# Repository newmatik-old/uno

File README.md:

# Uno

This is a complete package of files required to produce your own Arduino Uno. This serves as a demo repository for newmatik.com online PCBA customers to demo-price a project.

This package includes:

- CAD (Eagle board and schematic)
- Gerber Files
- PCB Specification
- Product Images
- Pick and Place File
- 3D Models

## Attributions

- Eagle board file and schematic, product image as well as dxf outlines from Arduino website (https://www.arduino.cc/en/Main/ArduinoBoardUno#documentation)

- Bill of Materials originally from Kitespace (https://github.com/kitspace-forks/arduino-uno)

- Collada and Sketchup 3D models from Trimble 3D Store, created by Engineer-Zero
  (https://3dwarehouse.sketchup.com/model/ee34d0b202060daa949ba13b9dbf2be2/Arduino-Uno?hl=de)

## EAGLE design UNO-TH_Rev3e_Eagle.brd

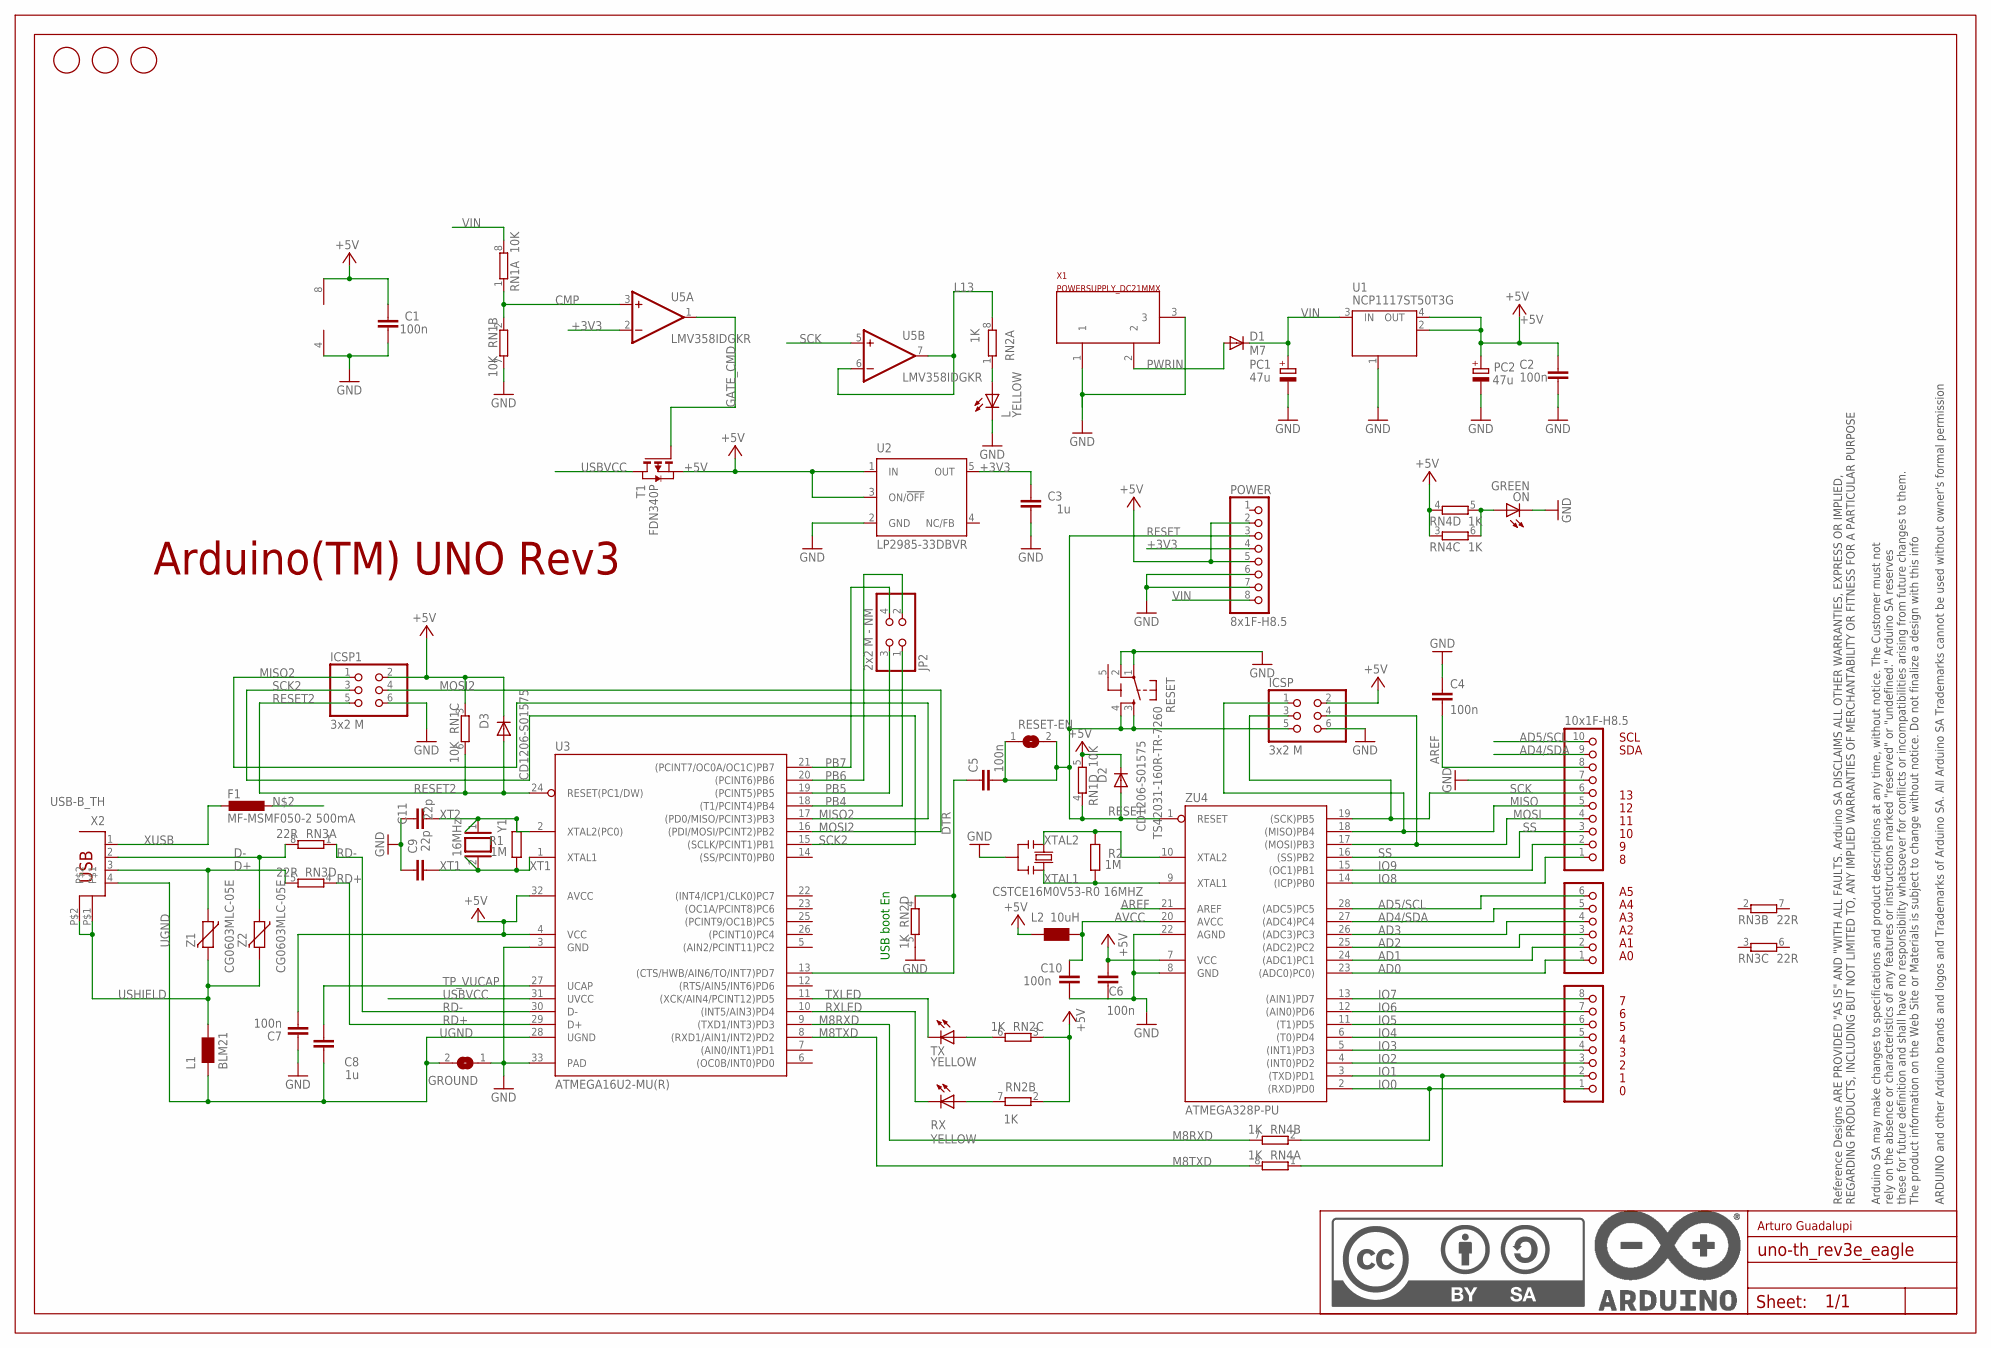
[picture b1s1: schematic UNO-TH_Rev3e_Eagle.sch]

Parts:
AD: 6x1F-H8.5; 1X06
C1, C2, C4, C5, C6, C7, C10: 100n; C0603-ROUND
C3, C8: 1u; C0603-ROUND
C9, C11: 22p; C0603-ROUND
D1: M7; SMB
D2, D3: CD1206-S01575; MINIMELF
F1: MF-MSMF050-2 500mA; L1812
FD1, FD2, FD3: FIDUCIALMOUNT; FIDUCIA-MOUNT
FRAME1: DNP; FRAME
GROUND: SJ
ICSP, ICSP1: 3x2 M; 2X03
IOH: 10x1F-H8.5; 1X10
IOL: 8x1F-H8.5; 1X08
JP2: 2x2 M - NM; 2X02
L: YELLOW; CHIP-LED0805
L1: BLM21; 0805
L2: 10uH; 0805
ON: GREEN; CHIP-LED0805
PC1, PC2: 47u; PANASONIC_D
POWER: 8x1F-H8.5; 1X08
R1, R2: 1M; R0603-ROUND
RESET: TS42031-160R-TR-7260; TS42
RESET-EN: SJ
RN1: 10K; CAY16
RN2, RN4: 1K; CAY16
RN3: 22R; CAY16
RX: YELLOW; CHIP-LED0805
T1: FDN340P; SOT-23
TX: YELLOW; CHIP-LED0805
U1: NCP1117ST50T3G; SOT223
U2: LP2985-33DBVR; SOT23-DBV
U3: ATMEGA16U2-MU(R); MLF32
U5: LMV358IDGKR; MSOP08
X1: POWERSUPPLY_DC21MMX; POWERSUPPLY_DC-21MM
X2: USB-B_TH; PN61729
Y1: 16MHz; QS
Y2: CSTCE16M0V53-R0 16MHZ; RESONATOR
Z1, Z2: CG0603MLC-05E; CT/CN0603
ZU4: ATMEGA328P-PU; DIL28-3

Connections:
5-GND: RESET.5 (5-GND)
+3V3: C3.2, POWER.4, U2.5 (OUT), U5.2 (-IN)
+5V: C1.2, C2.2, C6.2, C7.1, D2.C, D3.C, ICSP.2, ICSP1.2, L2.1, PC2.+, POWER.2, POWER.5, RN1.3 (1), RN1.5 (2), RN2.2 (1), RN2.3 (1), RN4.3 (1), RN4.4 (1), T1.2 (S), U1.2 (OUT), U1.4 (OUT), U2.1 (IN), U2.3 (ON/!OFF), U3.4 (VCC), U3.32 (AVCC), U5.8 (V+), ZU4.7 (VCC)
AD0: AD.1, ZU4.23 ((ADC0)PC0))
AD1: AD.2, ZU4.24 ((ADC1)PC1)
AD2: AD.3, ZU4.25 ((ADC2)PC2)
AD3: AD.4, ZU4.26 ((ADC3)PC3)
AD4/SDA: AD.5, IOH.9, ZU4.27 ((ADC4)PC4)
AD5/SCL: AD.6, IOH.10, ZU4.28 ((ADC5)PC5)
AREF: C4.2, IOH.8, ZU4.21 (AREF)
AVCC: C10.2, L2.2, ZU4.20 (AVCC)
CMP: RN1.1, RN1.2 (1), U5.3 (+IN)
D+: RN3.5 (2), X2.3, Z1.1
D-: RN3.8 (2), X2.2, Z2.1
DTR: C5.1, RN2.4 (1), U3.13 ((CTS/HWB/AIN6/TO/INT7)PD7)
GATE_CMD: T1.3 (G), U5.1 (OUT)
GND: C1.1, C2.1, C3.1, C4.1, C6.1, C7.2, C9.2, C10.1, C11.2, GROUND.1, ICSP.6, ICSP1.6, IOH.7, L.C, ON.C, PC1.-, PC2.-, POWER.6, POWER.7, RESET.1, RESET.2, RN1.7 (2), RN2.5 (2), U1.1 (GND/ADJ), U2.2 (GND), U3.3 (GND), U3.33 (PAD), U5.4 (V-), X1.1, X1.3, Y2.2, ZU4.8 (GND), ZU4.22 (AGND)
IO0: IOL.1, RN4.2 (1), ZU4.2 ((RXD)PD0)
IO1: IOL.2, RN4.1, ZU4.3 ((TXD)PD1)
IO2: IOL.3, ZU4.4 ((INT0)PD2)
IO3: IOL.4, ZU4.5 ((INT1)PD3)
IO4: IOL.5, ZU4.6 ((T0)PD4)
IO5: IOL.6, ZU4.11 ((T1)PD5)
IO6: IOL.7, ZU4.12 ((AIN0)PD6)
IO7: IOL.8, ZU4.13 ((AIN1)PD7)
IO8: IOH.1, ZU4.14 ((ICP)PB0)
IO9: IOH.2, ZU4.15 ((OC1)PB1)
L13: RN2.8 (2), U5.6 (-IN), U5.7 (OUT)
M8RXD: RN4.7 (2), U3.9 ((TXD1/INT3)PD3)
M8TXD: RN4.8 (2), U3.8 ((RXD1/AIN1/INT2)PD2)
MISO: ICSP.1, IOH.5, ZU4.18 ((MISO)PB4)
MISO2: ICSP1.1, U3.17 ((PD0/MISO/PCINT3)PB3)
MOSI: ICSP.4, IOH.4, ZU4.17 ((MOSI)PB3)
MOSI2: ICSP1.4, U3.16 ((PDI/MOSI/PCINT2)PB2)
unnamed: L.A, RN2.1
unnamed: ON.A, RN4.5 (2), RN4.6 (2)
unnamed: RN2.7 (2), RX.A
unnamed: RN2.6 (2), TX.A
PB4: JP2.1, U3.18 ((T1/PCINT4)PB4)
PB5: JP2.3, U3.19 ((PCINT5)PB5)
PB6: JP2.2, U3.20 ((PCINT6)PB6)
PB7: JP2.4, U3.21 ((PCINT7/OC0A/OC1C)PB7)
PWRIN: D1.A, X1.2
RD+: RN3.4 (1), U3.29 (D+)
RD-: RN3.1, U3.30 (D-)
RESET: C5.2, D2.A, ICSP.5, POWER.3, RESET.3, RESET.4, RESET-EN.1, RESET-EN.2, RN1.4 (1), ZU4.1 (RESET)
RESET2: D3.A, ICSP1.5, RN1.6 (2), U3.24 (RESET(PC1/DW))
RXLED: RX.C, U3.10 ((INT5/AIN3)PD4)
SCK: ICSP.3, IOH.6, U5.5 (+IN), ZU4.19 ((SCK)PB5)
SCK2: ICSP1.3, U3.15 ((SCLK/PCINT1)PB1)
SS: IOH.3, ZU4.16 ((SS)PB2)
TP_VUCAP: C8.1, U3.27 (UCAP)
TXLED: TX.C, U3.11 ((XCK/AIN4/PCINT12)PD5)
UGND: C8.2, GROUND.2, L1.1, U3.28 (UGND), X2.4
USBVCC: T1.1 (D), U3.31 (UVCC)
USHIELD: L1.2, X2.P$1, X2.P$2, Z1.2, Z2.2
VIN: D1.C, PC1.+, POWER.8, RN1.8 (2), U1.3 (IN)
XT1: C9.1, R1.1, U3.1 (XTAL1), Y1.2
XT2: C11.1, R1.2, U3.2 (XTAL2(PC0)), Y1.1
XTAL1: R2.1, Y2.3, ZU4.9 (XTAL1)
XTAL2: R2.2, Y2.1, ZU4.10 (XTAL2)
XUSB: F1.2, X2.1

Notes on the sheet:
Arduino(TM) UNO Rev3
USB boot En
SDA
SCL
Arturo Guadalupi

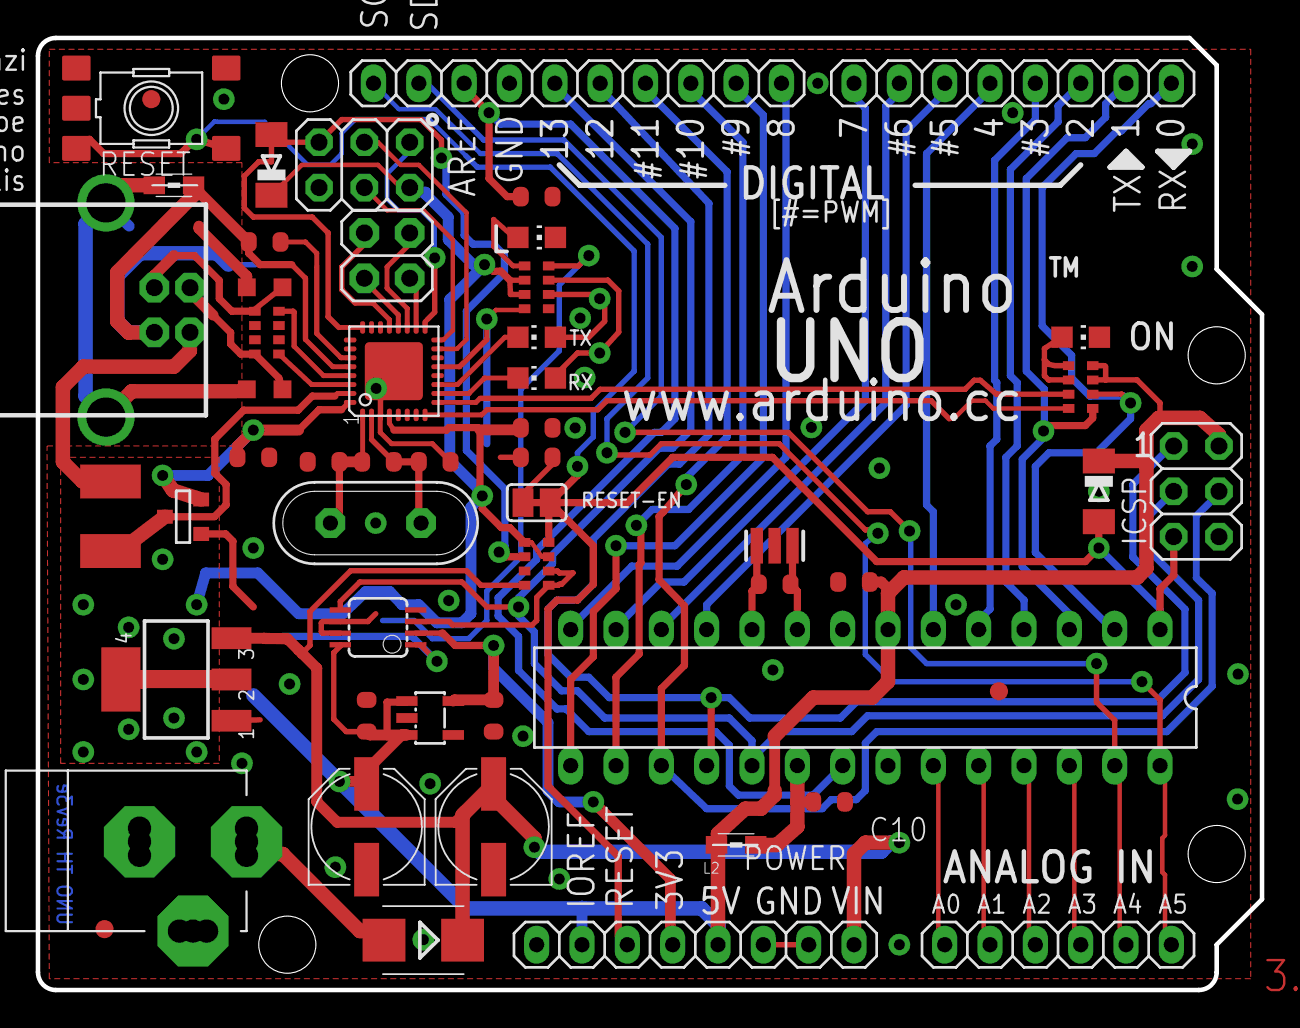
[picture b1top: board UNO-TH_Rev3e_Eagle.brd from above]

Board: 2 copper layers, 68.6 x 53.3 mm, 55 parts (1 on the bottom side), 61 nets.

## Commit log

2019-02-14 Add BOM
2019-02-14 Remove and Ignore MacOS DS_Store System Files
2019-02-14 Add PCB Specification
2019-02-14 Add 3D Models
2019-02-14 Add Readme and CAD Outlines
2019-03-20 Change Gerber Outline to .gm1

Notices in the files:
parts and their libraries:
Arduino-utility: Copyright (c) 2016-2017 Arduino LLC.  All right reserved.
